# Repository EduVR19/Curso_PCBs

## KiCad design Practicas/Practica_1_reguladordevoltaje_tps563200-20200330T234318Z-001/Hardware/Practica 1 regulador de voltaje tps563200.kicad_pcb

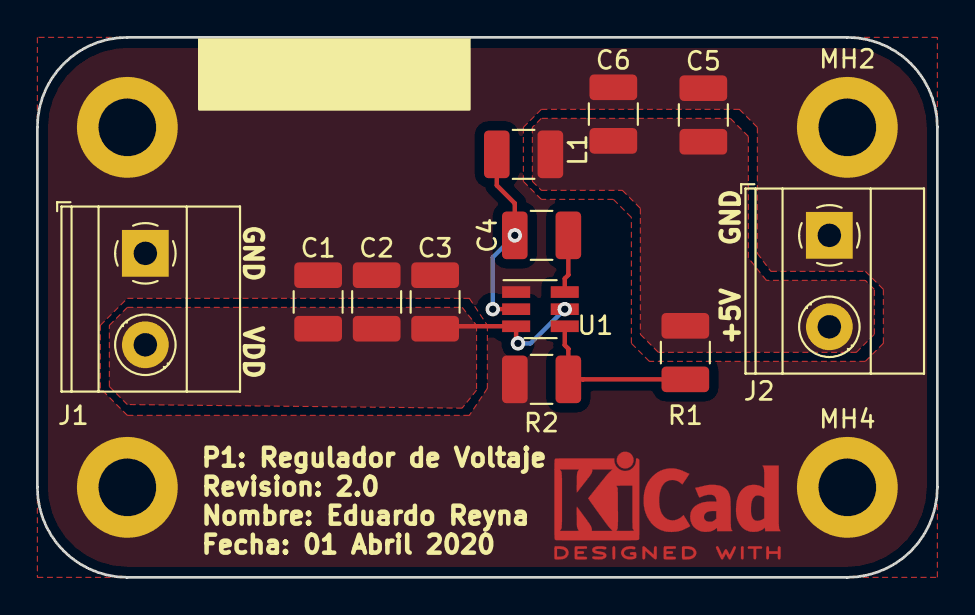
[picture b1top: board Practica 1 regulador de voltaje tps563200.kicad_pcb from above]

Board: 2 copper layers, 50.0 x 30.0 mm, 16 parts (0 on the bottom side), 6 nets.

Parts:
C1, C2: 10uF; C_1210_3225Metric_Pad1.42x2.65mm_HandSolder
C3, C4: 0.1uF; C_1210_3225Metric_Pad1.42x2.65mm_HandSolder
C5, C6: 22uF; C_1210_3225Metric_Pad1.42x2.65mm_HandSolder
J1, J2: Screw_Terminal_01x02; TerminalBlock_Phoenix_MKDS-1,5-2-5.08_1x02_P5.08mm_Horizont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
L1: 2.2uH; L_1210_3225Metric_Pad1.42x2.65mm_HandSolder
MH1, MH2, MH3, MH4: MountingHole_Pad; MountingHole_3.2mm_M3_DIN965_Pad
R1: 54.9K; R_1210_3225Metric_Pad1.42x2.65mm_HandSolder
R2: 10K; R_1210_3225Metric_Pad1.42x2.65mm_HandSolder
U1: TPS563200; SOT-23-6_Handsoldering

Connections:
+5V: C5.1, C6.1, J2.2, L1.2, R1.1
GND: C1.2, C2.2, C3.2, C5.2, C6.2, J1.1, J2.1, MH1.1, MH2.1, MH3.1, MH4.1, R2.2, U1.1
unnamed: C4.1, L1.1, U1.2
unnamed: C4.2, U1.6
unnamed: R1.2, R2.1, U1.4
VDD: C1.1, C2.1, C3.1, J1.2, U1.3, U1.5

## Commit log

2020-04-06 Se agrego un gitignore
2020-04-06 Version 1.0: Se realizo el ruteado sin hacer uso de los planos VDD, GND y +5V
2020-04-06 P1 Version 2.0: se realizo el ruteado con el uso de los planos, escribir texto e insertar logos o simbologia en forma de huellas
